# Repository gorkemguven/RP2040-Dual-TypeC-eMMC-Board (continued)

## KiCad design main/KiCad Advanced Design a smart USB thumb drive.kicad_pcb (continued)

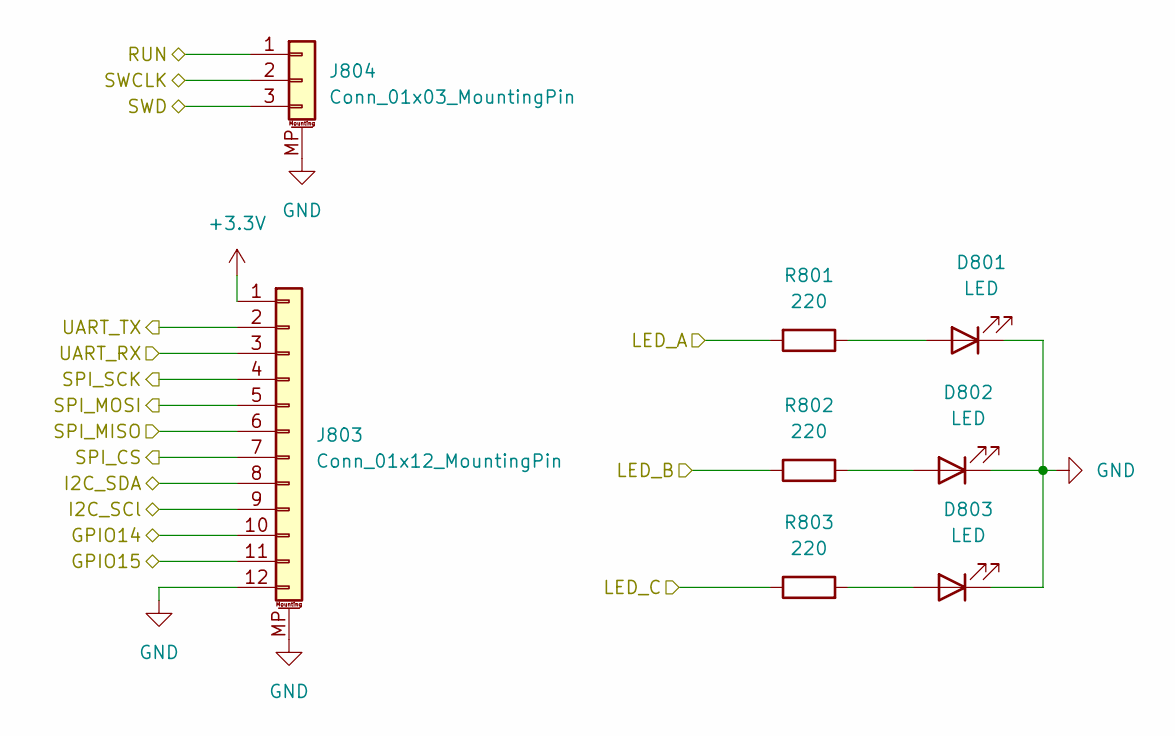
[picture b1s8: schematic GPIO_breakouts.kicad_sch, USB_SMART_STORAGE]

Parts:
D801, D802, D803: LED; LED_0603_1608Metric
J803: Conn_01x12_MountingPin; JST_SH_SM12B-SRSS-TB_1x12-1MP_P1.00mm_Horizontal
J804: Conn_01x03_MountingPin; JST_GH_SM03B-GHS-TB_1x03-1MP_P1.25mm_Horizontal
R801, R802, R803: 220; R_0402_1005Metric

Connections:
+3.3V: J803.1; also elsewhere on the board
/RP2040/GPIO14: J803.10; also elsewhere on the board
/RP2040/GPIO15: J803.11; also elsewhere on the board
/RP2040/I2C_SCL: J803.9; also elsewhere on the board
/RP2040/I2C_SDA: J803.8; also elsewhere on the board
/RP2040/LED_A: R801.2; also elsewhere on the board
/RP2040/LED_B: R802.1; also elsewhere on the board
/RP2040/LED_C: R803.1; also elsewhere on the board
/RP2040/RUN: J804.1; also elsewhere on the board
/RP2040/SPI_CS: J803.7; also elsewhere on the board
/RP2040/SPI_MISO: J803.6; also elsewhere on the board
/RP2040/SPI_MOSI: J803.5; also elsewhere on the board
/RP2040/SPI_SCK: J803.4; also elsewhere on the board
/RP2040/SWCLK: J804.2; also elsewhere on the board
/RP2040/SWD: J804.3; also elsewhere on the board
/RP2040/UART_RX: J803.3; also elsewhere on the board
/RP2040/UART_TX: J803.2; also elsewhere on the board
GND: D801.1 (K), D802.1 (K), D803.1 (K), J803.12, J803.MP (MountPin), J804.MP (MountPin); also elsewhere on the board
unnamed: D801.2 (A), R801.1
unnamed: D802.2 (A), R802.2
unnamed: D803.2 (A), R803.2

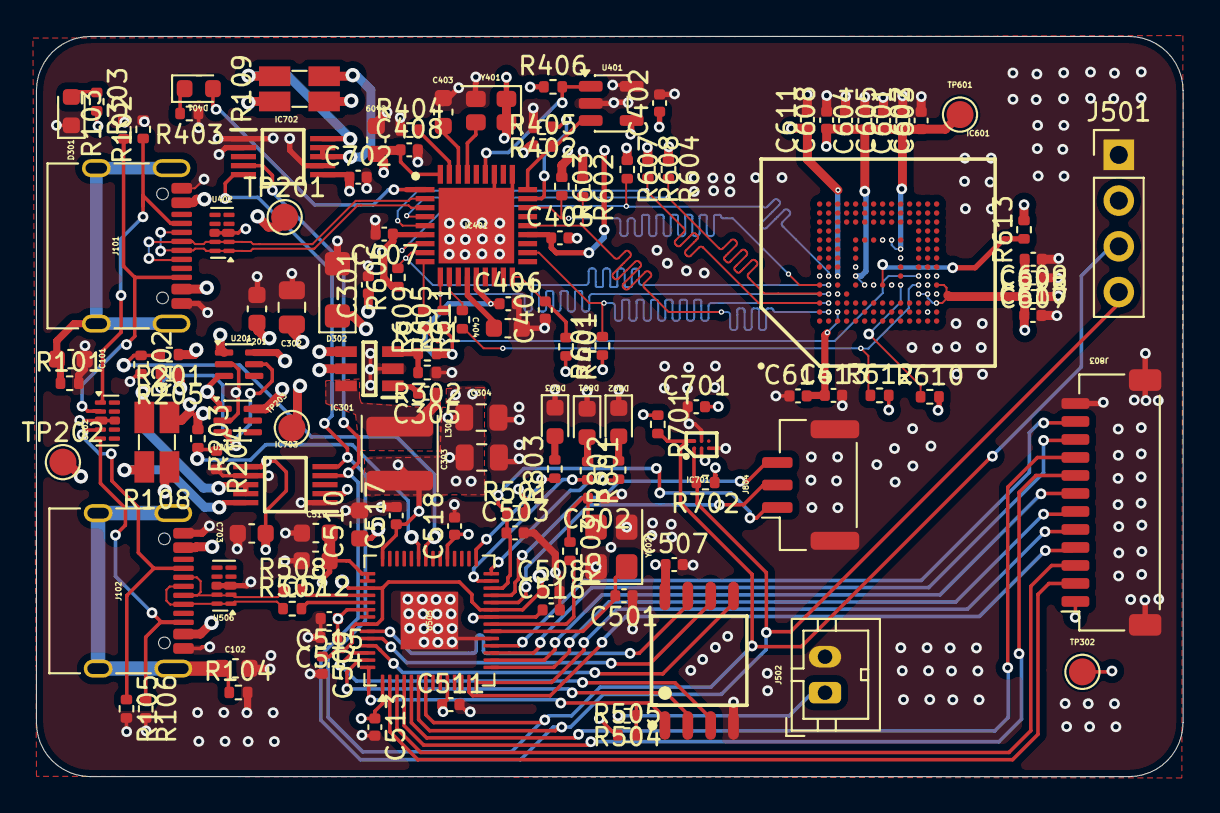
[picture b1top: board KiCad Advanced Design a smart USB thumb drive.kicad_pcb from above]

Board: 4 copper layers, 63.7 x 41.1 mm, 133 parts (0 on the bottom side), 87 nets.

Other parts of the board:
TP601: TestPoint; TestPoint_Pad_D1.5mm

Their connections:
+3.3V: TP601.1 (1_1); also elsewhere on the board
